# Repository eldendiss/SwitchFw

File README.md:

# SwitchFw — AVR HV Flyback PSU Controller

AVR firmware for the high-voltage flyback power supply that drives the Geiger-Müller tube.
It is a subsystem: the ESP32 (see `esp32-flyback-controller/`) is the system master and controls this AVR via I²C.

## Role in the system

```
ESP32 (master)  ──I²C──►  AVR SwitchFw (slave 0x2A)
                                │
                                ├─ PWM → MOSFET → flyback transformer → HV output
                                ├─ 4× relay range switches (R_SW network)
                                └─ Analog comparator OC protection
```

The ESP32 sets the target voltage (per-range setpoints), enables the supply via the EN line, and reads back feedback and fault status.

## Hardware

| Component | Part |
|-----------|------|
| MCU | ATmega328P (8 MHz) |
| Power switch | IRF540N + TC4420 gate driver |
| Voltage reference | LM4040 2.5 V shunt |
| Signal conditioning | LM321 op-amps |
| HV clamp | SMAJ150A TVS |
| Logic supply | LM317 → 5 V rail |

## Pin Map

| Pin | Dir | Signal |
|-----|-----|--------|
| PB1 | OUT | Gate drive (PWM, OC1A) |
| PC0 | IN  | HV feedback (ADC0, external AREF) |
| PC2 | OUT | OK LED |
| PC3 | OUT | Fault LED |
| PD3 | IN  | EN (active-high, external pull-down) |
| PD6 | IN  | OC comparator input (AIN0) |
| PB6 | OUT | R_SW0 (range relay 0) |
| PB7 | OUT | R_SW1 (range relay 1) |
| PD0 | OUT | R_SW2 (range relay 2) |
| PD1 | OUT | R_SW3 (range relay 3) |
| PC4 | I²C | SDA |
| PC5 | I²C | SCL |
| PD4 | —   | Free — connected to ESP32 |
| PD5 | —   | Free — connected to ESP32 |
| PB3/4/5, PC6 | ISP | MOSI/MISO/SCK/RESET |

> PD4 and PD5 were previously hardware range-select inputs. They are now free;
> range control is I²C-only.

## Firmware Overview

### PWM / control loop
- **Frequency**: 31.25 kHz, prescaler = 1, ICR1 = 255 (Fast PWM, TOP = ICR1)
- **Duty ceiling**: 20% hard cap (software and hardware)
- **Loop rate**: 1 kHz PI+D controller
- **Feedback**: ADC0, 8× boxcar average, ~125 kHz conversion rate
- **Timebase**: Timer2, prescaler /8 → 1 µs tick, 32-bit `us_now32()`

### Control phases

| Phase | Description |
|-------|-------------|
| `PH_PRECHARGE` | Fixed small duty soft-start until time elapsed and FB threshold reached |
| `PH_PI` | Closed-loop PI + filtered derivative on measured FB |

### Regulation modes

| Mode | Description |
|------|-------------|
| `REG_PWM` | Continuous PWM regulation |
| `REG_PFM` | Hysteretic microburst: fires a short burst when FB drops below the lower threshold, then coasts; quieter at light load |

### Fault protection
- **OV**: ADC-based, per-range trip/clear thresholds; latches until FB drops below clear level
- **OC**: Analog comparator (AIN0 vs 1.1 V bandgap), cycle-by-cycle hard gate kill; blanking window at each period start avoids switch-edge noise

### Range switching
A safe open → wait-stable → make sequence prevents false OC/OV trips during relay transitions:
1. Open all R_SW outputs
2. Wait ≥ 5 ms and `|dFB/dt|` ≤ threshold
3. Close requested R_SW

### Power saving when EN is deasserted
When EN is low the firmware:
- Forces gate off (PWM disabled)
- Stops the ADC free-run (saves ~350 µA + eliminates 125 kHz ISR load)
- Disables Timer1 OVF/COMPB ISRs (was 31 k interrupts/s, only needed when switching)
- Disarms the analog comparator
- Puts the CPU into `SLEEP_MODE_IDLE`

Timer2 OVF (every 256 µs) and I²C events wake the CPU for housekeeping. Estimated MCU current drops from ~10 mA to ~2–3 mA.

### EEPROM configuration
- Slot size: 128 B, CRC-16 protected
- Wear leveling: automatic slot rotation
- On boot: loads valid slot or writes defaults and continues

## I²C Protocol (slave 0x2A)

Register-pointer scheme: first byte of a write sets the pointer, subsequent bytes are data.

### Register map

| Address | Name | Access | Description |
|---------|------|--------|-------------|
| 0x00–0x01 | `fb_set_cnt` | R/W | Active setpoint (ADC counts) |
| 0x02–0x03 | `fb_ov_trip_cnt` | R/W | Active OV trip threshold |
| 0x04–0x05 | `fb_ov_clear_cnt` | R/W | Active OV clear threshold |
| 0x06–0x0D | `fb_set_cnt_tab[4]` | R/W | Per-range setpoints (R0–R3, u16 LE) |
| 0x0E–0x15 | `fb_ov_trip_cnt_tab[4]` | R/W | Per-range OV trip thresholds |
| 0x16–0x1D | `fb_ov_clear_cnt_tab[4]` | R/W | Per-range OV clear thresholds |
| 0x1E–… | *(rest of ControlParams)* | R/W | Gains, PFM settings, timing, etc. |
| 0x20 | `range_req` | R/W | Write 0–3 to request range switch; read = last request |
| 0x21 | `range_src` | R/W | 0=legacy HW (treated as I²C), **1=I²C (default)**, 2=AUTO |
| 0x40 | `cmd` | W | Command (see below); read returns 0x00 |
| 0x50–0x57 | `status` | R | 8-byte status block (see below) |

All multi-byte fields are **little-endian**. Config reads auto-increment the pointer (up to 16 bytes per `onRequest`).

### Commands (0x40)
| Code | Action |
|------|--------|
| 0x01 | Save current config to EEPROM |
| 0x02 | Reset controller to `PH_PRECHARGE` |

### Status block (0x50, 8 bytes)

| Bytes | Field | Description |
|-------|-------|-------------|
| 0 | *(reserved)* | Always 0 |
| 1 | *(reserved)* | Always 0 |
| 2–3 | `fb_ema` | EMA-filtered feedback (ADC counts, u16 LE) |
| 4–5 | *(reserved)* | Always 0 |
| 6 | `active_range` | Currently engaged range (0–3) |
| 7 | `range_busy` | 1 while relay transition is in progress |

## LED patterns (OK LED, PC2)

| State | Pattern |
|-------|---------|
| Waiting for EN | Short 120 ms blip every 1 s |
| Precharge | Fast blink ~5 Hz |
| Ramping | Medium blink ~2.5 Hz |
| Regulating (PWM) | Steady ON |
| PFM hold | 1 Hz blink |
| Range switching | Double-blink |

Fault LED (PC3) blinks N times (pause, repeat) where N = fault code: 1 = OC, 2 = OV.

## Build

```
PlatformIO, AVR-GCC toolchain.
Programmer: ISP (USBasp, AVR Dragon, etc.) via ISP header.
```

---

## License

Non-Commercial. Free for personal, educational, and research use.
Commercial use or redistribution for profit requires written permission. See [LICENSE](./LICENSE).

> ⚠️ This device generates potentially lethal high voltages. Only qualified personnel should work on it.

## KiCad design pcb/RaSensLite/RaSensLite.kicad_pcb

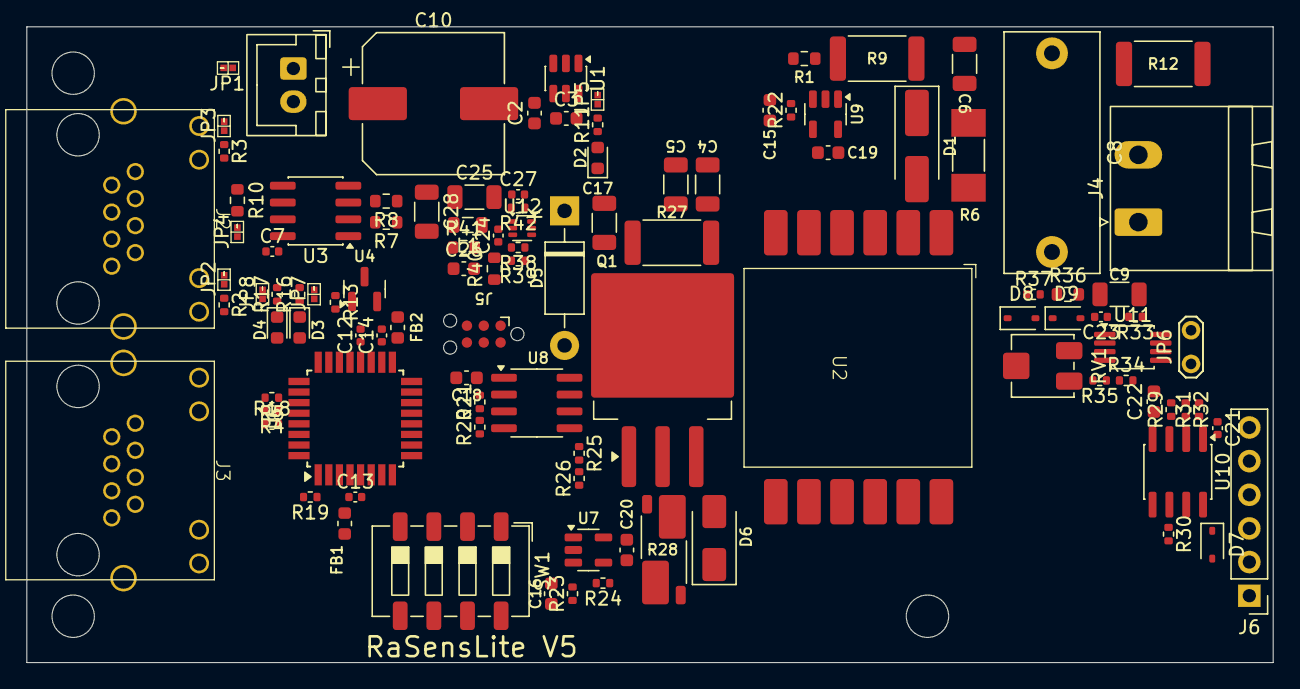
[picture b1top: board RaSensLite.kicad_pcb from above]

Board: 2 copper layers, 94.1 x 48.0 mm, 109 parts (0 on the bottom side), 77 nets, no tracks yet.

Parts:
C2: 2n2; C_0603_1608Metric
C3, C18, C19, C20: 100n; C_0603_1608Metric
C4, C5: 2u2; C_1206_3216Metric
C6: 100p; C_1206_3216Metric
C7, C12, C13, C14, C21, C27: 100n; C_0402_1005Metric
C8: ECW-FD2J105PQ; C_Rect_L18.0mm_W7.0mm_P15.00mm_FKS3_FKP3
C9: 10p; C_1206_3216Metric
C10: EEE-FN1C102UP; CP_Elec_10x10.5
C15: 22n; C_0603_1608Metric
C16: 220p; C_0603_1608Metric
C17: 1n; C_1206_3216Metric
C22: 100p; C_0603_1608Metric
C23: 0u1; C_0402_1005Metric
C24: 1u; C_0402_1005Metric
C25, C28: 22u; C_1206_3216Metric
C26: 10p; C_0603_1608Metric
D1: VS-E7MH0112; D_SMA_Handsoldering
D2: LED; LED_0603_1608Metric
D3: STATUS1; LED_0603_1608Metric
D4: STATUS2; LED_0603_1608Metric
D5: UF4007; D_DO-41_SOD81_P10.16mm_Horizontal
D6: SMAJ150A; D_SMA
D7: D_Schottky; D_SOD-323
D8, D9: 1N5819WS; D_SOD-323
FB1, FB2: BLM18AG601SN1; L_0603_1608Metric
H1, H2, H3: MountingHole; MountingHole_3.2mm_M3_ISO7380
J1: Conn_01x02; JST_XH_B2B-XH-A_1x02_P2.50mm_Vertical
J2, J3: RJ45_LED_Shielded; MTJ-88ARX1-FSM-PG-LH
J4: Conn_01x02; PhoenixContact_MSTBA_2,5_2-G-5,08_1x02_P5.08mm_Horizontal
J5: TC2030; Tag-Connect_TC2030-IDC-NL_2x03_P1.27mm_Vertical
J6: Conn_01x06_Socket; PinHeader_1x06_P2.54mm_Vertical
JP1, JP2, JP3, JP4, JP5, JP7, JP8: Jumper_2_Small_Open; JUMPER_SMD_1x2_tiny
JP6: Jumper_2_Open; TestPoint_2Pads_Pitch2.54mm_Drill0.8mm
L1: LSANB2016KKT4R7M; L_0805_2012Metric
Q1: IPP075N15N3; TO-263-3_TabPin2
R1: 10k; R_0603_1608Metric
R2, R3, R16, R17, R21, R22, R29: 1k; R_0402_1005Metric
R4, R5, R13, R18, R19, R24, R35: 10k; R_0402_1005Metric
R6: MMP100FRF100R; R_MELF_MMB-0207
R7, R8: 0; R_0603_1608Metric
R9: HV733ATTE4304F; R_2512_6332Metric
R10: 120; R_0603_1608Metric
R11: 4k7; R_0402_1005Metric
R12: HV733ATTE2004F; R_2512_6332Metric
R20, R26, R39: 47k; R_0402_1005Metric
R23: 91k; R_0402_1005Metric
R25, R38: 10; R_0402_1005Metric
R27: 330; R_2512_6332Metric
R28: 140m; R_Shunt_Vishay_WSK2512_6332Metric_T2.21mm
R30: 470; R_0402_1005Metric
R31: 330k; R_0402_1005Metric
R32: 1Meg; R_0402_1005Metric
R33: 1M; R_0402_1005Metric
R34, R37, R42: 100k; R_0402_1005Metric
R36: 59k; R_0603_1608Metric
R40: 7k68; R_0603_1608Metric
R41: 40k2; R_0603_1608Metric
RV1: 3314J-1-504E; Potentiometer_Bourns_3314J_Vertical
SW1: SW_DIP_x04; SW_DIP_SPSTx04_Slide_6.7x11.72mm_W6.73mm_P2.54mm_LowProfile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
U1: TPS22810DBV; SOT-23-6
U2: DA2032-AL
U3: SN65HVD1781; SOIC-8_3.9x4.9mm_P1.27mm
U4: LM4040DBZ-2.5; SOT-23
U6: ATmega328P-A; TQFP-32_7x7mm_P0.8mm
U7, U9: LM321; SOT-23-5
U8: TC4420; SOIC-8_3.9x4.9mm_P1.27mm
U10: ATtiny412-SS; SOIC-8_3.9x4.9mm_P1.27mm
U11: LT1711xMS8; MSOP-8_3x3mm_P0.65mm
U12: MP1476; SOT-563

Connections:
+5V: C7.2, C19.2, C20.2, C21.2, C23.1, C26.1, C28.2, D8.1 (K), FB1.1, FB2.1, J5.2, J6.4, L1.2, R4.2, R5.2, R13.1, R18.1, R41.1, RV1.2, U3.8 (VCC), U7.5 (V+), U9.5 (V+), U10.1 (VCC), U11.1 (V+)
/A: J2.7, J3.7, R10.1, U3.6 (A)
/ADDR0: SW1.2, U6.12 (PB0)
/ADDR1: SW1.1, U6.14 (PB2)
/ADDR2: SW1.4, U6.7 (XTAL1/PB6)
/ADDR3: SW1.3, U6.8 (XTAL2/PB7)
/B: J2.8, J3.8, JP4.1 (A), U3.7 (B)
/Comparator/IN: C9.2, R36.2
/Comparator/OUT: JP6.2 (B), R33.1, U11.7 (Q)
/D: R8.2, U6.31 (PD1)
/GEIGER_OUTPUT: JP6.1 (A), R29.2
/LINK: J2.12, U6.9 (PD5)
/PSU_EN: J2.5, J3.5, R19.1, U6.1 (PD3)
/PWR_EN: J2.4, J3.4, U1.3 (EN/UVLO)
/Pulse CNT/UPDI: D7.2 (A), J6.2, R30.2
/R: R7.1, U6.30 (PD0)
/RE/DE: J2.10, U3.2 (~RE), U3.3 (DE), U6.2 (PD4)
/SCL: R4.1, U6.28 (PC5), U10.5 (PA2)
/SDA: R5.1, U6.27 (PC4), U10.4 (PA1)
/VIN: C10.1, J1.1, JP1.1 (A), U1.1 (VIN)
/VIN_RJ: J2.2, J2.6, J3.2, J3.6, JP1.2 (B)
/VIN_SW: C3.2, C4.1, C5.1, C17.2, C18.2, C25.2, C27.1, JP5.2 (B), R27.1, R32.1, R42.2, U1.5 (QOD), U1.6 (VOUT), U2.3, U2.4, U2.5, U2.6, U8.1 (VDD), U8.8 (VDD), U12.1 (IN)
/switcher/AD0: C15.2, R22.1, U6.23 (PC0)
/switcher/AIN1: C16.1, R23.1, U6.10 (PD6), U7.4
/switcher/FB: R1.2, R9.1, U9.1 (+)
/switcher/GATE: R25.1, U8.6 (OUTPUT), U8.7 (OUTPUT)
/switcher/MISO: J5.1, U6.16 (PB4)
/switcher/MOSI: J5.4, U6.15 (PB3)
/switcher/PWM: R20.2, R21.1, U6.13 (PB1)
/switcher/RST: J5.5, R18.2, U6.29 (~RESET/PC6)
/switcher/SCK: J5.3, U6.17 (PB5)
/switcher/SHUNT_N: R24.1, R28.3
/switcher/SHUNT_P: R28.2, U7.1 (+)
/switcher/STATUS0: D3.2 (A), U6.25 (PC2)
/switcher/STATUS1: D4.2 (A), U6.26 (PC3)
/switcher/T-: D5.2 (A), D6.1 (A1), Q1.2 (D), U2.7, U2.8, U2.9, U2.10
GND: C2.1, C3.1, C4.2, C5.2, C7.1, C8.2, C10.2, C12.2, C13.2, C14.2, C15.1, C18.1, C19.1, C20.1, C21.1, C22.2, C23.2, C25.1, C27.2, C28.1, D2.1 (K), D9.2 (A), J1.2, J2.1, J2.3, J3.1, J3.3, J4.2, J5.6, J6.6, JP2.2 (B), JP3.2 (B), JP7.1 (A), JP8.1 (A), R1.1, R19.2, R20.1, R28.4, R31.2, R34.2, R37.1, R40.1, SW1.5, SW1.6, SW1.7, SW1.8, U1.2 (GND), U2.12, U3.5 (GND), U4.2 (A), U6.3 (GND), U6.5 (GND), U6.21 (GND), U7.2 (V-), U8.4 (GND), U8.5 (GND), U9.2 (V-), U10.8 (GND), U11.4 (V-), U11.5 (LATCH), U11.6 (GND), U12.3 (GND)
unnamed: C6.1, R6.2
unnamed: C13.1, FB1.2, U6.4 (VCC), U6.6 (VCC)
unnamed: C24.1, R38.2
unnamed: C26.2, R39.2, R40.2, R41.2
unnamed: D1.2 (A), R6.1, U2.1
unnamed: C6.2, C8.1, D1.1 (K), R9.2, R12.1
unnamed: D2.2 (A), R11.1
unnamed: D3.1 (K), R16.1
unnamed: D4.1 (K), R17.1
unnamed: C17.1, D5.1 (K), R27.2
unnamed: D6.2 (A2), Q1.3 (S), R26.1, R28.1
unnamed: D7.1 (K), J6.3
unnamed: D8.2 (A), D9.1 (K), R33.2, R36.1, R37.2, U11.2 (+)
unnamed: J2.9, R2.2
unnamed: J2.11, R3.2
unnamed: C9.1, J4.1, R12.2
unnamed: JP2.1 (A), R2.1
unnamed: JP3.1 (A), R3.1
unnamed: JP4.2 (B), R10.2
unnamed: JP5.1 (A), R11.2
unnamed: JP7.2 (B), R16.2
unnamed: JP8.2 (B), R17.2
unnamed: Q1.1 (G), R25.2, R26.2
unnamed: R35.2, RV1.1
unnamed: C2.2, U1.4 (CT)
unnamed: R8.1, U3.4 (D)
unnamed: R7.2, U3.1 (R)
unnamed: C12.1, R13.2, U4.1 (K), U6.20 (AREF)
unnamed: C14.1, FB2.2, U6.18 (AVCC)
unnamed: C16.2, R23.2, R24.2, U7.3 (-)
unnamed: R21.2, U8.2 (INPUT)
unnamed: R22.2, U9.3 (-), U9.4
unnamed: R31.1, R32.2, U10.2 (PA6)
unnamed: C22.1, R29.1, U10.3 (PA7)
unnamed: R30.1, U10.6 (~RESET/PA0)
unnamed: R34.1, R35.1, U11.3 (-)
unnamed: R38.1, U12.4 (BST)
unnamed: R42.1, U12.5 (EN)
unnamed: R39.1, U12.6 (FB)
unnamed: C24.2, L1.1, U12.2 (SW)

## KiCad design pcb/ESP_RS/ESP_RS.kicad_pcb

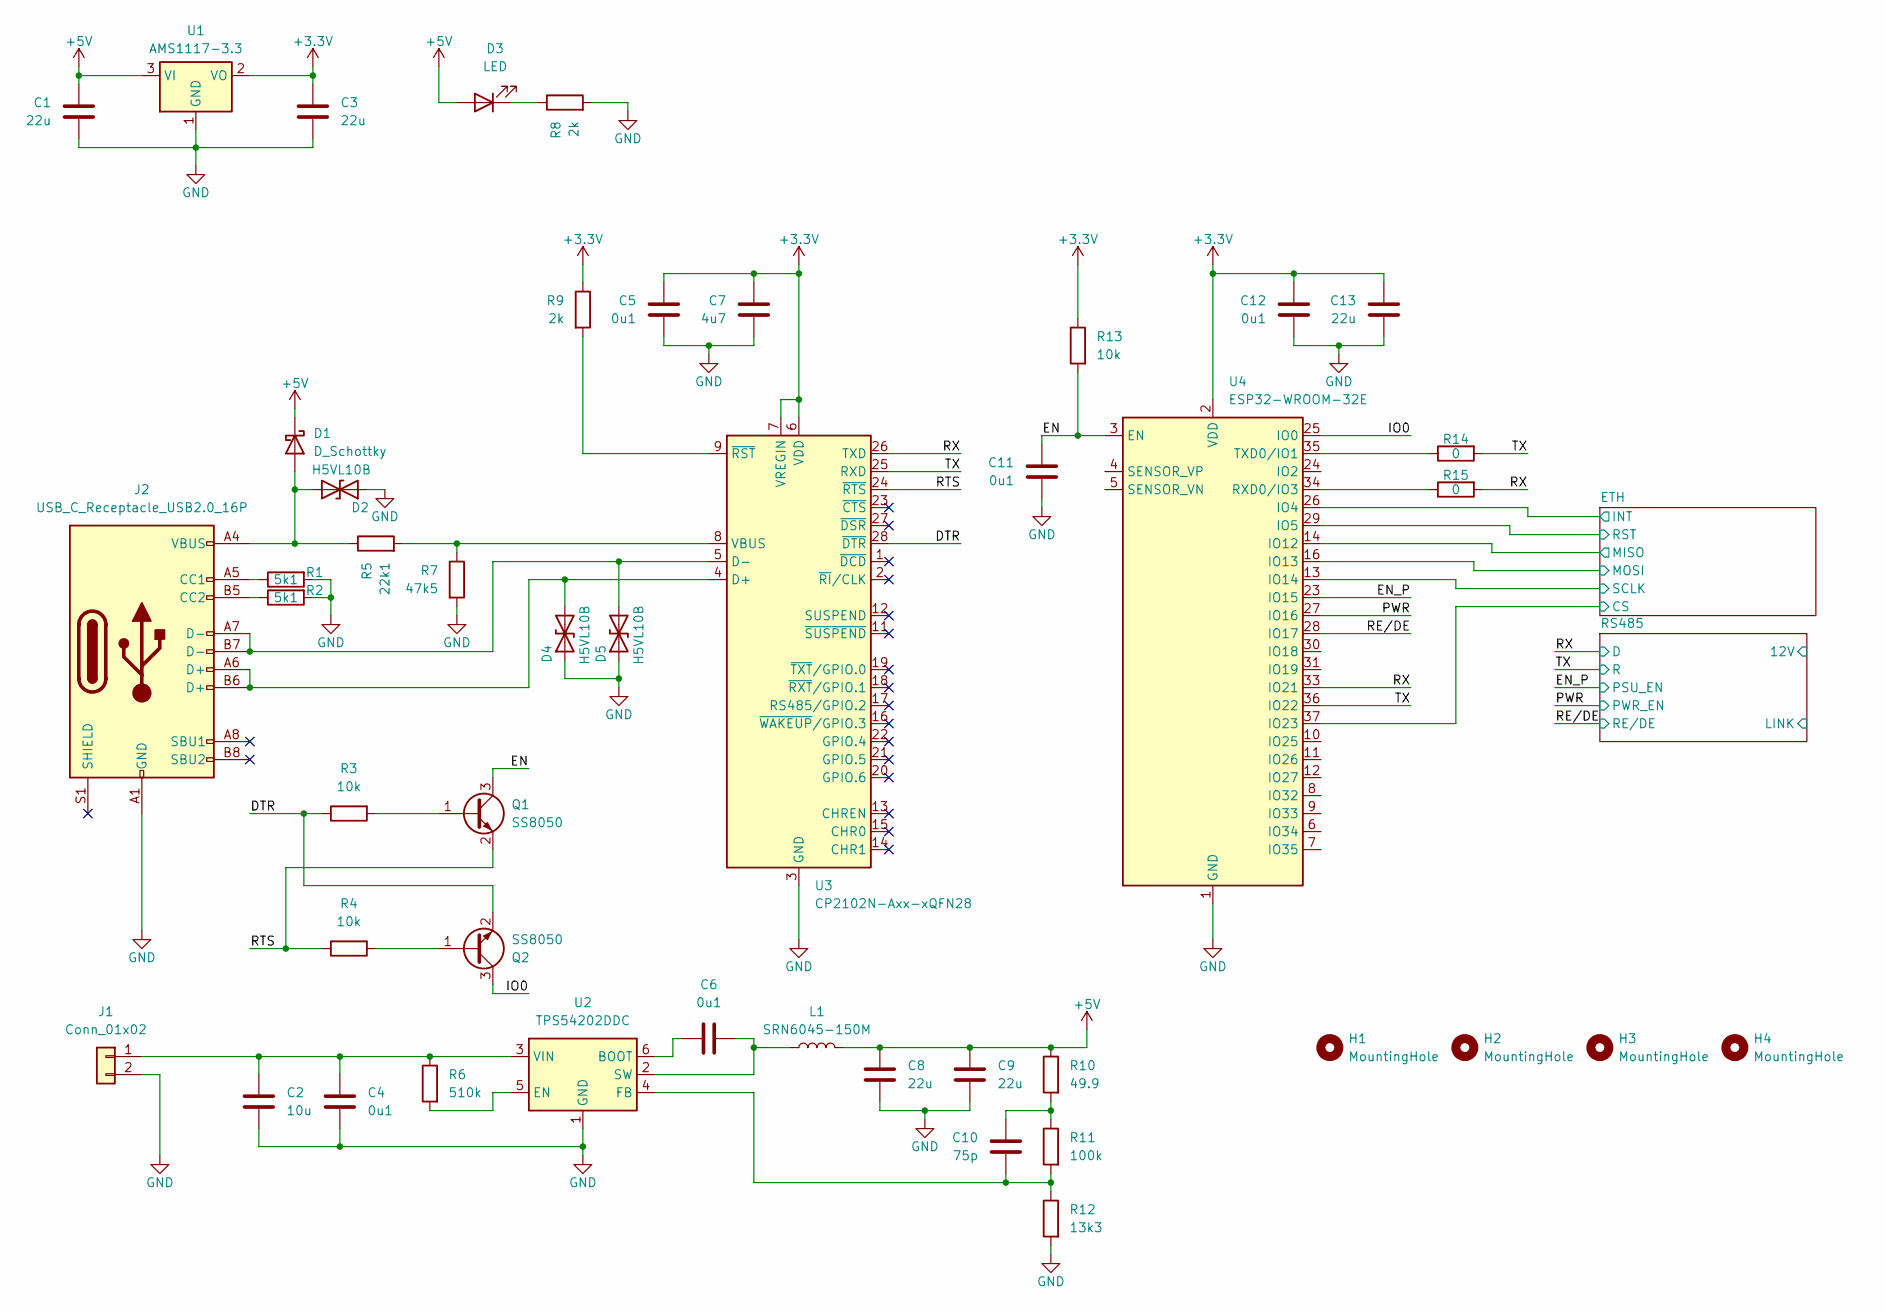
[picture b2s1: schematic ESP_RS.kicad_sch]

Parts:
C1, C3, C8, C9, C13: 22u; C_0603_1608Metric
C2: 10u; C_0805_2012Metric
C4, C6: 0u1; C_0805_2012Metric
C5, C11, C12: 0u1; C_0603_1608Metric
C7: 4u7; C_0603_1608Metric
C10: 75p; C_0603_1608Metric
D1: D_Schottky; D_SOD-323
D2, D4, D5: H5VL10B; D_SOD-882
D3: LED; LED_0603_1608Metric
H1, H2, H3, H4: MountingHole; MountingHole_3.2mm_M3_DIN965
J1: Conn_01x02; JST_XH_B2B-XH-AM_1x02_P2.50mm_Vertical
J2: USB_C_Receptacle_USB2.0_16P; USB_C_Receptacle_GCT_USB4105-xx-A_16P_TopMnt_Horizontal
L1: SRN6045-150M; L_Bourns_SRN6045TA
Q1, Q2: SS8050; SOT-23
R1, R2: 5k1; R_0603_1608Metric
R3, R4, R13: 10k; R_0603_1608Metric
R5: 22k1; R_0603_1608Metric
R6: 510k; R_0603_1608Metric
R7: 47k5; R_0603_1608Metric
R8, R9: 2k; R_0603_1608Metric
R10: 49.9; R_0603_1608Metric
R11: 100k; R_0603_1608Metric
R12: 13k3; R_0603_1608Metric
R14, R15: 0; R_0603_1608Metric
U1: AMS1117-3.3; SOT-223-3_TabPin2
U2: TPS54202DDC; SOT-23-6
U3: CP2102N-Axx-xQFN28; QFN-28-1EP_5x5mm_P0.5mm_EP3.35x3.35mm
U4: ESP32-WROOM-32E; ESP32-WROOM-32D

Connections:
+3.3V: C3.1, C5.1, C7.1, C12.1, C13.1, R9.1, R13.1, U1.2 (VO), U3.6 (VDD), U3.7 (VREGIN), U4.2 (VDD); also elsewhere on the board
+5V: C1.1, C8.1, C9.1, D1.1 (K), D3.2 (A), L1.2, R10.1, U1.3 (VI); also elsewhere on the board
/DTR: Q2.2 (E), R3.1, U3.28 (~DTR)
/EN: C11.1, Q1.3 (C), R13.2, U4.3 (EN)
/EN_P: U4.23 (IO15); also elsewhere on the board
/ETH/CS: U4.37 (IO23); also elsewhere on the board
/ETH/INT: U4.26 (IO4); also elsewhere on the board
/ETH/MISO: U4.14 (IO12); also elsewhere on the board
/ETH/MOSI: U4.16 (IO13); also elsewhere on the board
/ETH/RST: U4.29 (IO5); also elsewhere on the board
/ETH/SCLK: U4.13 (IO14); also elsewhere on the board
/IO0: Q2.3 (C), U4.25 (IO0)
/PWR: U4.27 (IO16); also elsewhere on the board
/RE/DE: U4.28 (IO17); also elsewhere on the board
/RTS: Q1.2 (E), R4.1, U3.24 (~RTS)
/RX: R15.2, U3.26 (TXD), U4.33 (IO21); also elsewhere on the board
/TX: R14.2, U3.25 (RXD), U4.36 (IO22); also elsewhere on the board
GND: C1.2, C2.2, C3.2, C4.2, C5.2, C7.2, C8.2, C9.2, C11.2, C12.2, C13.2, D2.1 (A1), D4.1 (A1), D5.1 (A1), J1.2, J2.A1 (GND), J2.A12 (GND), J2.B1 (GND), J2.B12 (GND), R1.2, R2.2, R7.2, R8.2, R12.2, U1.1 (GND), U2.1 (GND), U3.3 (GND), U3.29 (GND), U4.1 (GND), U4.15 (GND), U4.38 (GND), U4.39 (GND); also elsewhere on the board
unnamed: C10.1, R10.2, R11.1
unnamed: D1.2 (A), D2.2 (A2), J2.A4 (VBUS), J2.A9 (VBUS), J2.B4 (VBUS), J2.B9 (VBUS), R5.1
unnamed: D3.1 (K), R8.1
unnamed: D4.2 (A2), J2.A6 (D+), J2.B6 (D+), U3.4 (D+)
unnamed: D5.2 (A2), J2.A7 (D-), J2.B7 (D-), U3.5 (D-)
unnamed: C2.1, C4.1, J1.1, R6.1, U2.3 (VIN)
unnamed: J2.A5 (CC1), R1.1
unnamed: J2.B5 (CC2), R2.1
unnamed: Q1.1 (B), R3.2
unnamed: Q2.1 (B), R4.2
unnamed: C6.1, U2.6 (BOOT)
unnamed: R6.2, U2.5 (EN)
unnamed: C10.2, R11.2, R12.1, U2.4 (FB)
unnamed: C6.2, L1.1, U2.2 (SW)
unnamed: R5.2, R7.1, U3.8 (VBUS)
unnamed: R9.2, U3.9 (~RST)
unnamed: R15.1, U4.34 (RXD0/IO3)
unnamed: R14.1, U4.35 (TXD0/IO1)

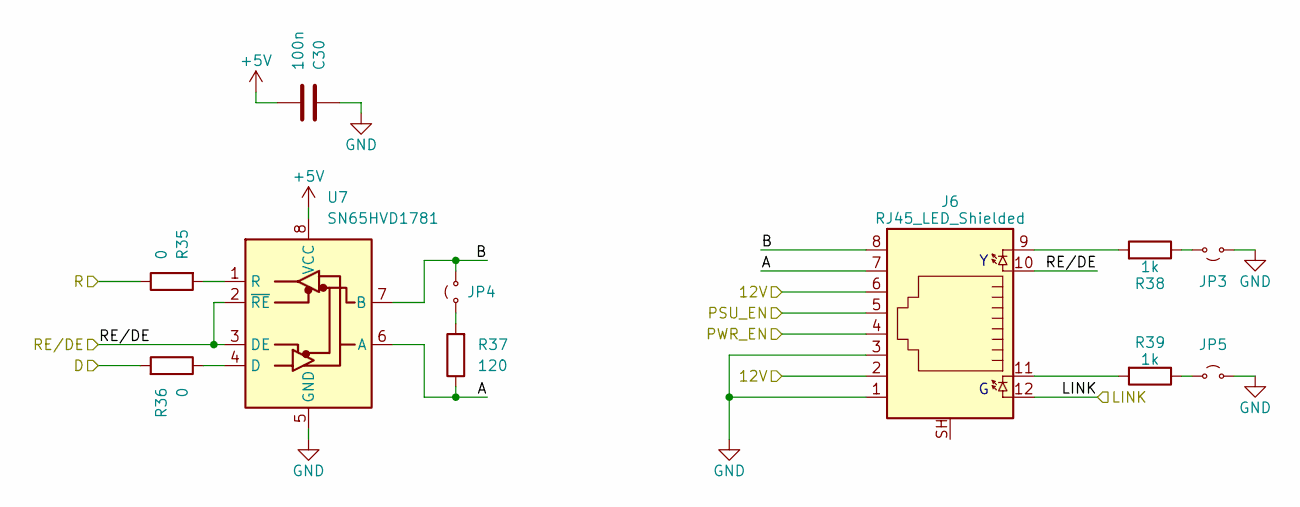
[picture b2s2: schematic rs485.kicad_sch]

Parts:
C30: 100n; C_0402_1005Metric
J6: RJ45_LED_Shielded; MTJ-88ARX1-FSM-PG-LH
JP3, JP4, JP5: Jumper_2_Small_Open; JUMPER_SMD_1x2_tiny
R35, R36: 0; R_0603_1608Metric
R37: 120; R_0603_1608Metric
R38, R39: 1k; R_0402_1005Metric
U7: SN65HVD1781; SOIC-8_3.9x4.9mm_P1.27mm

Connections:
+5V: C30.2, U7.8 (VCC); also elsewhere on the board
/EN_P: J6.5; also elsewhere on the board
/PWR: J6.4; also elsewhere on the board
/RE/DE: J6.10, U7.2 (~RE), U7.3 (DE); also elsewhere on the board
/RS485/12V: J6.2, J6.6
/RS485/A: J6.7, R37.1, U7.6 (A)
/RS485/B: J6.8, JP4.1 (A), U7.7 (B)
/RS485/LINK: J6.12
/RX: R36.2; also elsewhere on the board
/TX: R35.1; also elsewhere on the board
GND: C30.1, J6.1, J6.3, JP3.2 (B), JP5.2 (B), U7.5 (GND); also elsewhere on the board
unnamed: J6.9, R38.2
unnamed: J6.11, R39.2
unnamed: JP3.1 (A), R38.1
unnamed: JP4.2 (B), R37.2
unnamed: JP5.1 (A), R39.1
unnamed: R36.1, U7.4 (D)
unnamed: R35.2, U7.1 (R)

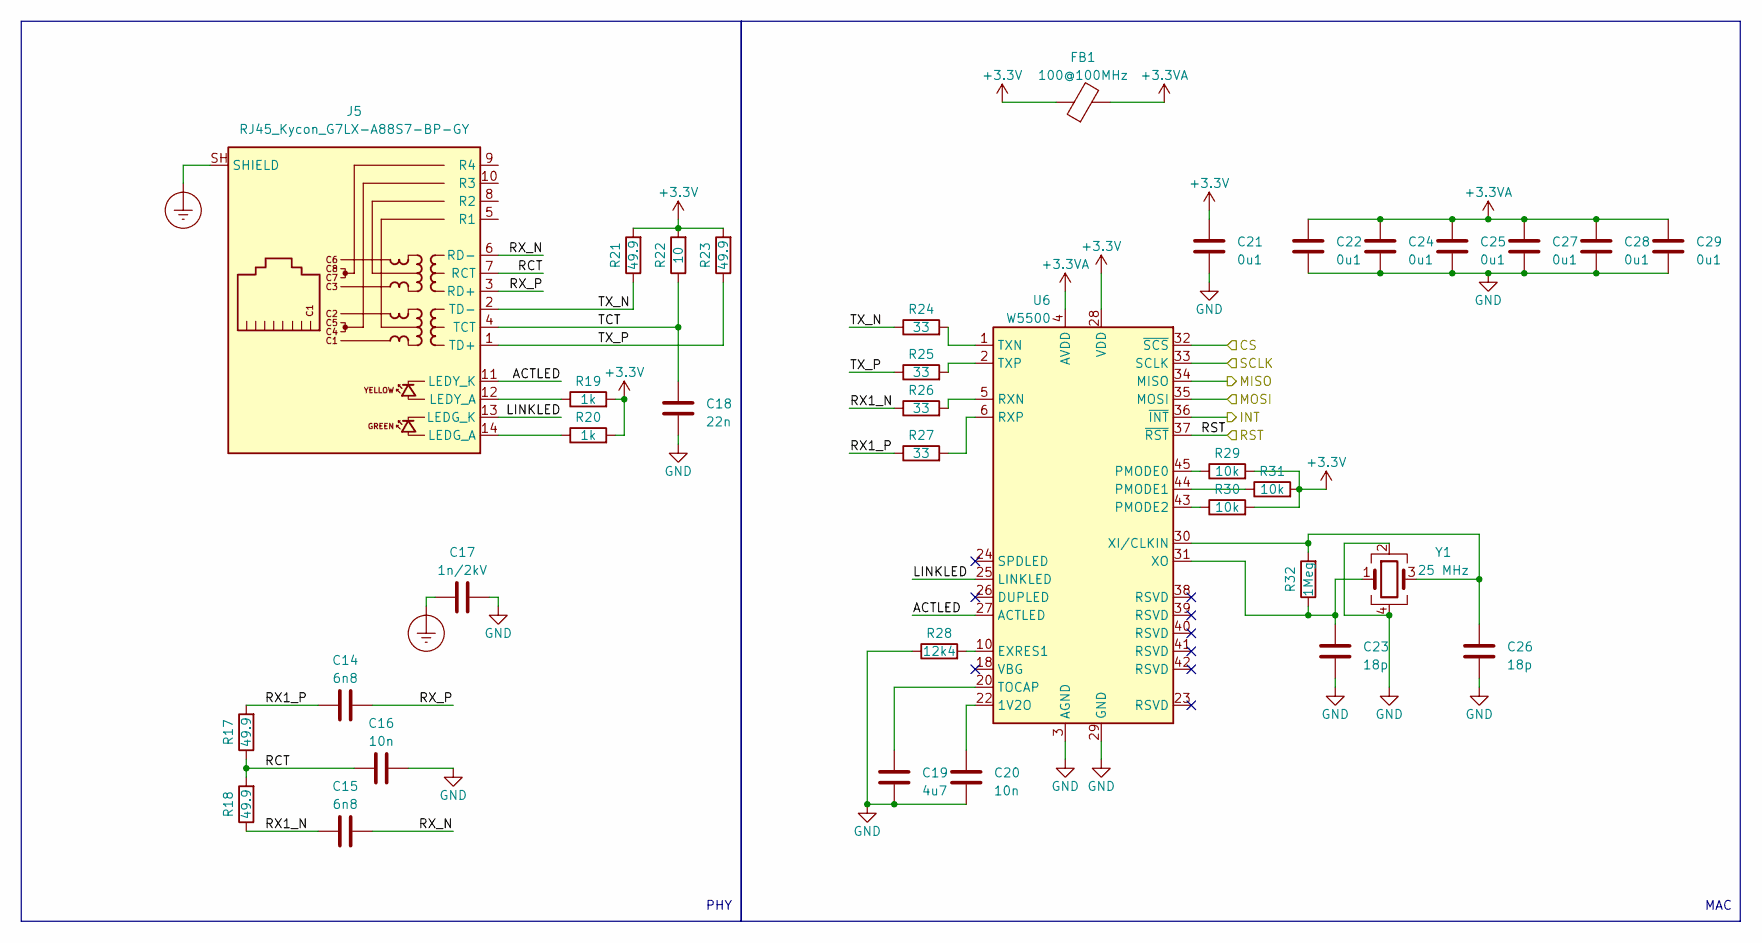
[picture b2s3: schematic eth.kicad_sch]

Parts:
C14, C15: 6n8; C_0603_1608Metric
C16, C20: 10n; C_0603_1608Metric
C17: 1n/2kV; C_1206_3216Metric
C18: 22n; C_0603_1608Metric
C19: 4u7; C_0603_1608Metric
C21, C22, C24, C25, C27, C28, C29: 0u1; C_0603_1608Metric
C23, C26: 18p; C_0603_1608Metric
FB1: 100@100MHz; L_0603_1608Metric
J5: RJ45_Kycon_G7LX-A88S7-BP-GY; RJ45_Kycon_G7LX-A88S7-BP-xx_Horizontal
R17, R18, R21, R23: 49.9; R_0402_1005Metric
R19, R20: 1k; R_0402_1005Metric
R22: 10; R_0402_1005Metric
R24, R25, R26, R27: 33; R_0402_1005Metric
R28: 12k4; R_0402_1005Metric
R29, R30, R31: 10k; R_0402_1005Metric
R32: 1Meg; R_0402_1005Metric
U6: W5500; LQFP-48_7x7mm_P0.5mm
Y1: 25 MHz; Crystal_SMD_Abracon_ABM8AIG-4Pin_3.2x2.5mm

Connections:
+3.3V: C21.1, FB1.1, R19.2, R20.2, R21.2, R22.2, R23.2, R29.2, R30.2, R31.2, U6.28 (VDD); also elsewhere on the board
+3.3VA: C22.1, C24.1, C25.1, C27.1, C28.1, C29.1, FB1.2, U6.4 (AVDD), U6.8 (AVDD), U6.11 (AVDD), U6.15 (AVDD), U6.17 (AVDD), U6.21 (AVDD)
/ETH/ACTLED: J5.11 (LEDY_K), U6.27 (ACTLED)
/ETH/CS: U6.32 (~SCS); also elsewhere on the board
/ETH/INT: U6.36 (~INT); also elsewhere on the board
/ETH/LINKLED: J5.13 (LEDG_K), U6.25 (LINKLED)
/ETH/MISO: U6.34 (MISO); also elsewhere on the board
/ETH/MOSI: U6.35 (MOSI); also elsewhere on the board
/ETH/RCT: C16.1, J5.7 (RCT), R17.1, R18.2
/ETH/RST: U6.37 (~RST); also elsewhere on the board
/ETH/RX1_N: C15.1, R18.1, R26.1
/ETH/RX1_P: C14.1, R17.2, R27.1
/ETH/RX_N: C15.2, J5.6 (RD-)
/ETH/RX_P: C14.2, J5.3 (RD+)
/ETH/SCLK: U6.33 (SCLK); also elsewhere on the board
/ETH/TCT: C18.1, J5.4 (TCT), R22.1
/ETH/TX_N: J5.2 (TD-), R21.1, R24.1
/ETH/TX_P: J5.1 (TD+), R23.1, R25.1
Earth_Protective: C17.1, J5.SH (SHIELD)
GND: C16.2, C17.2, C18.2, C19.2, C20.2, C21.2, C22.2, C23.2, C24.2, C25.2, C26.2, C27.2, C28.2, C29.2, R28.1, U6.3 (AGND), U6.9 (AGND), U6.14 (AGND), U6.16 (AGND), U6.19 (AGND), U6.29 (GND), U6.48 (AGND), Y1.2, Y1.4; also elsewhere on the board
unnamed: J5.14 (LEDG_A), R20.1
unnamed: J5.12 (LEDY_A), R19.1
unnamed: C20.1, U6.22 (1V2O)
unnamed: R28.2, U6.10 (EXRES1)
unnamed: R29.1, U6.45 (PMODE0)
unnamed: R31.1, U6.44 (PMODE1)
unnamed: R30.1, U6.43 (PMODE2)
unnamed: R26.2, U6.5 (RXN)
unnamed: R27.2, U6.6 (RXP)
unnamed: C19.1, U6.20 (TOCAP)
unnamed: R24.2, U6.1 (TXN)
unnamed: R25.2, U6.2 (TXP)
unnamed: C26.1, R32.2, U6.30 (XI/CLKIN), Y1.3
unnamed: C23.1, R32.1, U6.31 (XO), Y1.1

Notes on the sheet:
MAC
PHY

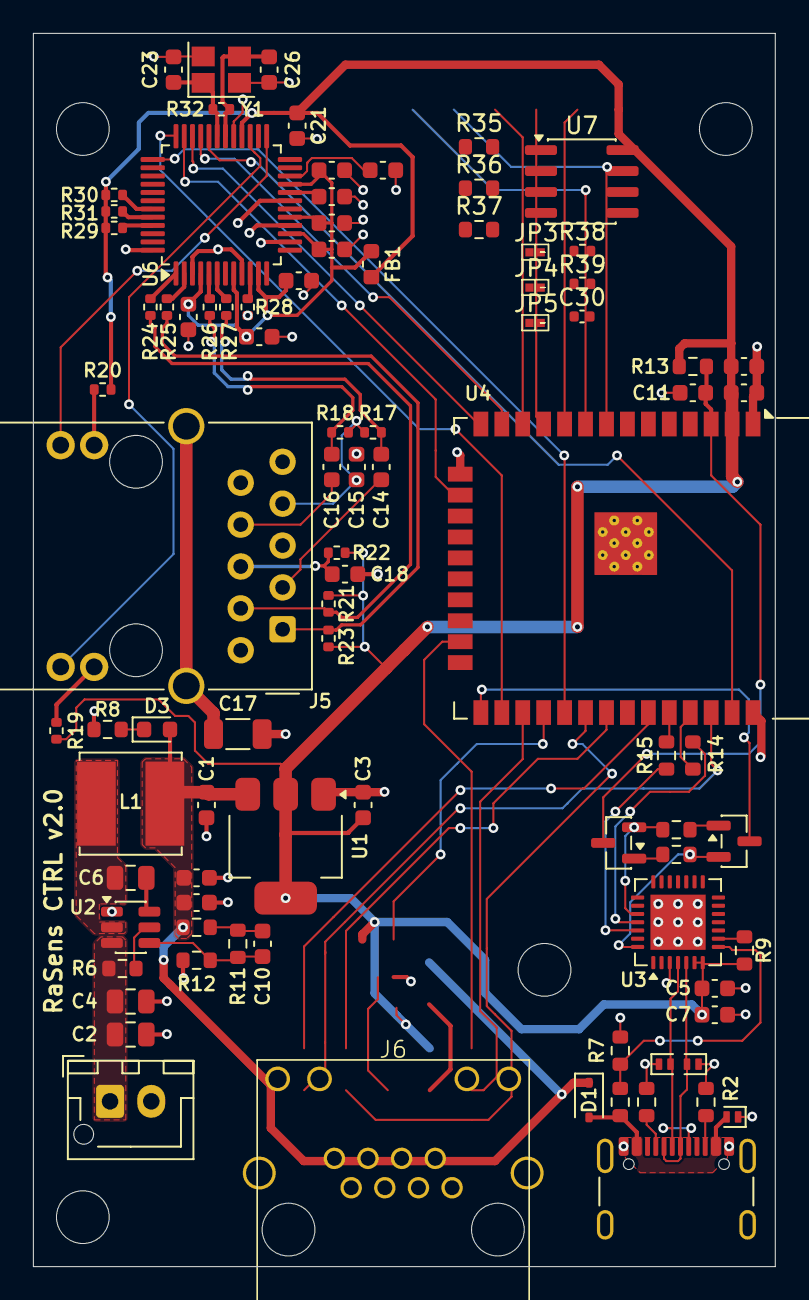
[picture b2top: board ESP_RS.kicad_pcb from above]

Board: 2 copper layers, 45.0 x 74.8 mm, 93 parts (0 on the bottom side), 72 nets.

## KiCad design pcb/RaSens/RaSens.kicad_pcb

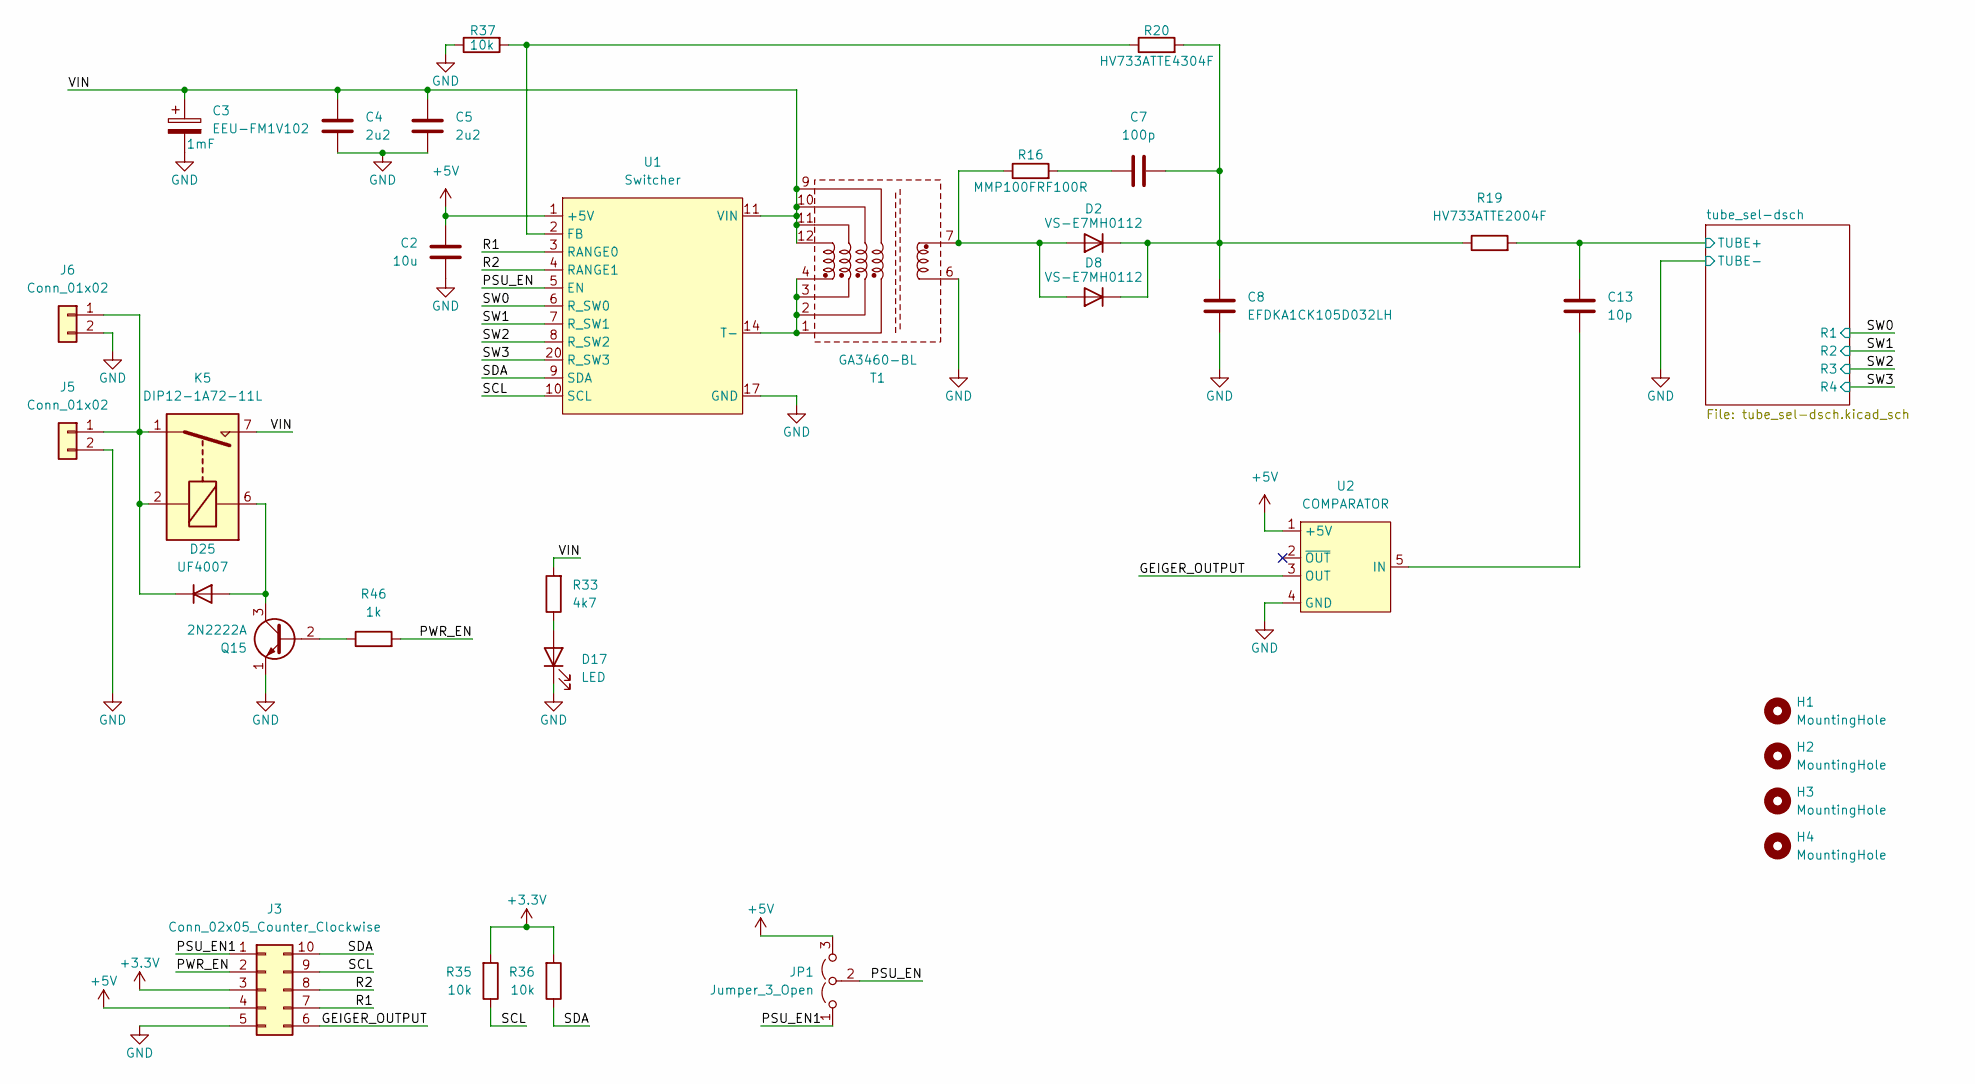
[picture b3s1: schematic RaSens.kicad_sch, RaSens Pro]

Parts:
C2: 10u; C_1206_3216Metric
C3: EEU-FM1V102; CP_Radial_D12.5mm_P5.00mm
C4, C5: 2u2; C_1206_3216Metric
C7: 100p; C_1206_3216Metric
C8: EFDKA1CK105D032LH; C_Rect_L31.5mm_W11.0mm_P27.50mm_MKS4
C13: 10p; C_1206_3216Metric
D2, D8: VS-E7MH0112; D_SMA-SMB_Universal_Handsoldering
D17: LED; LED_0603_1608Metric
D25: UF4007; D_DO-41_SOD81_P10.16mm_Horizontal
H1, H2, H3, H4: MountingHole; MountingHole_3.2mm_M3_ISO7380
J3: Conn_02x05_Counter_Clockwise; IDC-Header_2x05_P2.54mm_Horizontal
J5, J6: Conn_01x02; JST_XH_B2B-XH-A_1x02_P2.50mm_Vertical
JP1: Jumper_3_Open; PinHeader_1x03_P2.54mm_Vertical
K5: DIP12-1A72-11L; Relay_StandexMeder_DIP_LowProfile
Q15: 2N2222A; TO-92L_Inline
R16: MMP100FRF100R; R_MELF_MMB-0207
R19: HV733ATTE2004F; R_2512_6332Metric
R20: HV733ATTE4304F; R_2512_6332Metric
R33: 4k7; R_0603_1608Metric
R35, R36, R37: 10k; R_0603_1608Metric
R46: 1k; R_0805_2012Metric
T1: GA3460-BL; GA3460
U1: Switcher
U2: COMPARATOR

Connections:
+3.3V: J3.3, R35.2, R36.2
+5V: C2.1, J3.4, JP1.3 (B), U1.1 (+5V), U2.1 (+5V); also elsewhere on the board
/GEIGER_OUTPUT: J3.6, U2.3 (OUT)
/PSU_EN: JP1.2 (C), U1.5 (EN)
/PSU_EN1: J3.1, JP1.1 (A)
/PWR_EN: J3.2, R46.2
/R1: J3.7, U1.3 (RANGE0)
/R2: J3.8, U1.4 (RANGE1)
/SCL: J3.9, R35.1, U1.10 (SCL)
/SDA: J3.10, R36.1, U1.9 (SDA)
/SW0: U1.6 (R_SW0); also elsewhere on the board
/SW1: U1.7 (R_SW1); also elsewhere on the board
/SW2: U1.8 (R_SW2); also elsewhere on the board
/SW3: U1.20 (R_SW3); also elsewhere on the board
/VIN: C3.1, C4.1, C5.1, K5.7, K5.8, R33.2, T1.9, T1.10, T1.11, T1.12, U1.11 (VIN), U1.12 (VIN), U1.13 (VIN)
/tube_sel-dsch/TUBE+: C13.1, R19.2; also elsewhere on the board
GND: C2.2, C3.2, C4.2, C5.2, C8.2, D17.1 (K), J3.5, J5.2, J6.2, Q15.1 (E), R37.1, T1.6, U1.17 (GND), U1.18 (GND), U1.19 (GND), U2.4 (GND); also elsewhere on the board
unnamed: C7.1, R16.2
unnamed: C13.2, U2.5 (IN), U2.6 (IN), U2.7 (IN), U2.8 (IN)
unnamed: D2.2 (A), D8.2 (A), R16.1, T1.7
unnamed: C7.2, C8.1, D2.1 (K), D8.1 (K), R19.1, R20.2
unnamed: D17.2 (A), R33.1
unnamed: D25.2 (A), K5.6, Q15.3 (C)
unnamed: D25.1 (K), J5.1, J6.1, K5.1, K5.2, K5.14
unnamed: Q15.2 (B), R46.1
unnamed: T1.1, T1.2, T1.3, T1.4, U1.14 (T-), U1.15 (T-), U1.16 (T-)
unnamed: R20.1, R37.2, U1.2 (FB)

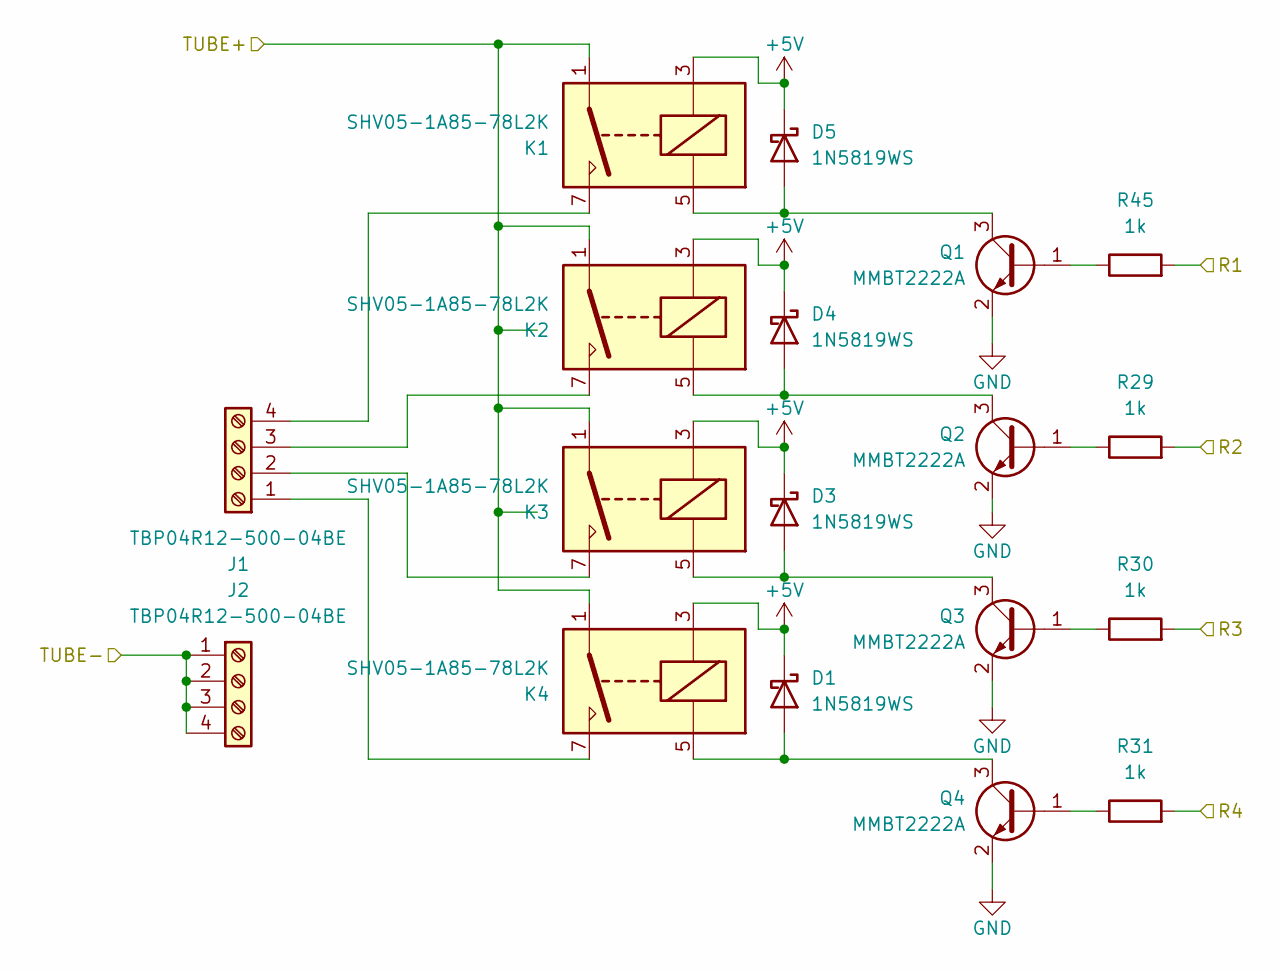
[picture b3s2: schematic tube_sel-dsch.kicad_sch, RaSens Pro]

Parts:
D1, D3, D4, D5: 1N5819WS; D_SOD-323
J1, J2: TBP04R12-500-04BE; PhoenixContact_MSTBA_2,5_4-G_1x04_P5.00mm_Horizontal
K1, K2, K3, K4: SHV05-1A85-78L2K; MEDER_SHV
Q1, Q2, Q3, Q4: MMBT2222A; SOT-23
R29, R30, R31, R45: 1k; R_0805_2012Metric

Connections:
+5V: D1.1 (K), D3.1 (K), D4.1 (K), D5.1 (K), K1.3, K2.3, K3.3, K4.3; also elsewhere on the board
/SW0: R45.2; also elsewhere on the board
/SW1: R29.2; also elsewhere on the board
/SW2: R30.2; also elsewhere on the board
/SW3: R31.2; also elsewhere on the board
/tube_sel-dsch/TUBE+: K1.1, K2.1, K3.1, K4.1; also elsewhere on the board
GND: J2.1, J2.2, J2.3, J2.4, Q1.2 (E), Q2.2 (E), Q3.2 (E), Q4.2 (E); also elsewhere on the board
unnamed: D1.2 (A), K4.5, Q4.3 (C)
unnamed: D3.2 (A), K3.5, Q3.3 (C)
unnamed: D4.2 (A), K2.5, Q2.3 (C)
unnamed: D5.2 (A), K1.5, Q1.3 (C)
unnamed: J1.1, K4.7
unnamed: J1.2, K3.7
unnamed: J1.3, K2.7
unnamed: J1.4, K1.7
unnamed: Q1.1 (B), R45.1
unnamed: Q2.1 (B), R29.1
unnamed: Q3.1 (B), R30.1
unnamed: Q4.1 (B), R31.1

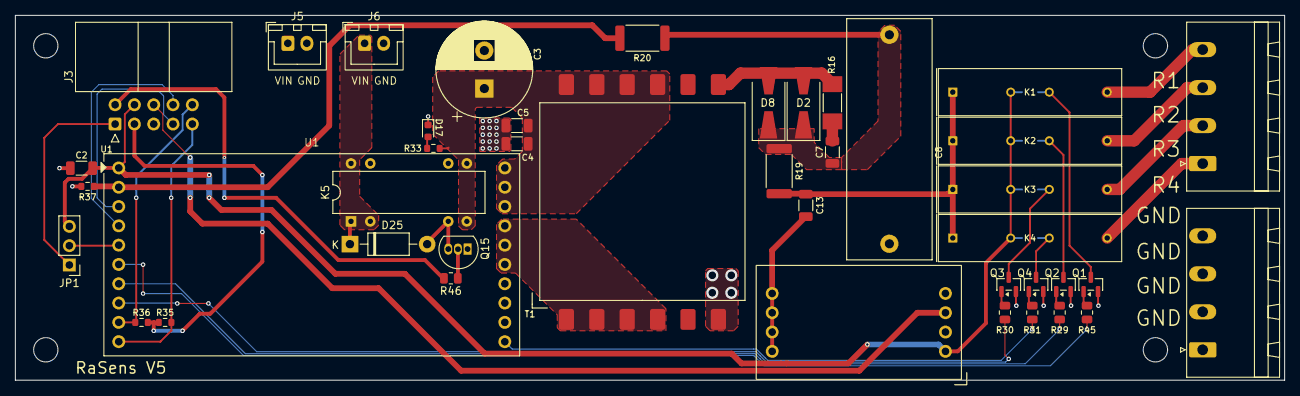
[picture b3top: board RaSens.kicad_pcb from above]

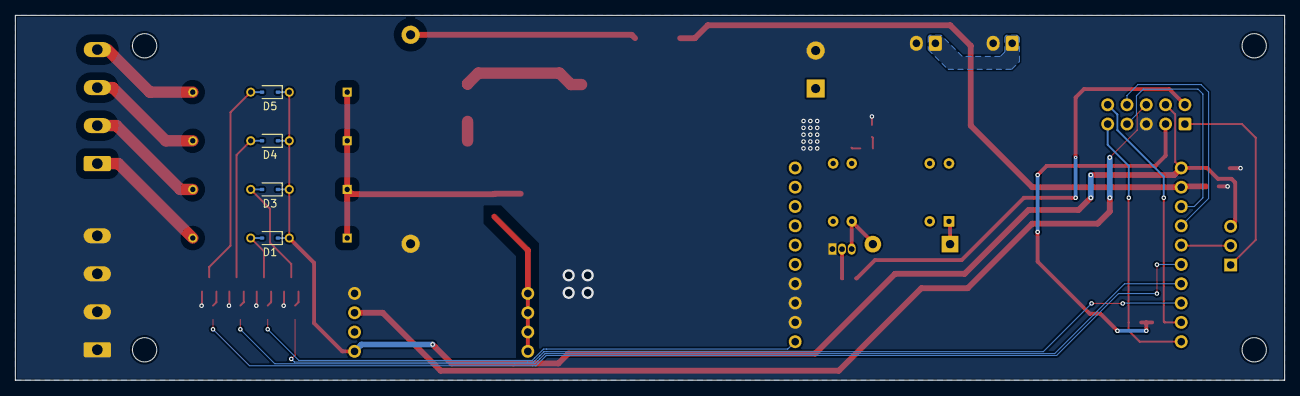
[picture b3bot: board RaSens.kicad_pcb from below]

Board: 2 copper layers, 167.0 x 48.0 mm, 50 parts (4 on the bottom side), 39 nets.
